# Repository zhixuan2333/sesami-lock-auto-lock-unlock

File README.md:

# Sesami Lock MitoLab

自動施錠・解錠スケジューラー — Seeed XIAO ESP32C6 + DS1302 RTC + SESAME スマートロック

[English](README.en.md)

---

> **免責事項**: このプロジェクトのコード・ドキュメントはすべて AI (Claude) によって生成されています。動作保証はなく、作者は一切の責任を負いません。自己責任でご使用ください。

---

## 概要

設定した時刻に SESAME スマートロックを自動で施錠・解錠します。DS1302 RTC で正確な時刻を保持し、ESP32C6 のディープスリープを活用して低消費電力を実現します。起動時にシリアルシェルが立ち上がり、時刻やスケジュールをその場で設定できます。

---

## ハードウェア

| 部品 | 型番 |
| --- | --- |
| マイコン | Seeed Studio XIAO ESP32C6 |
| RTC | DS1302 (+ 32.768 kHz 水晶) |
| スマートロック | SESAME 3/4/5/5 PRO など |

---

## 回路図

```text
                    XIAO ESP32C6
                  ┌─────────────┐
              D0  │●           ●│ 5V
              D1  │●           ●│ GND
              D2  │●           ●│ 3V3
              D3  │●           ●│ D10 ──── CLK (SCL)
              D4  │●           ●│ D9  ──── DAT (IO)
              D5  │●           ●│ D8  ──── RST
              D6  │●           ●│ D7
                  └─────────────┘
                                             DS1302
                                          ┌──────────┐
                              3V3 ────── │ VCC      │
                              GND ────── │ GND      │
                        CLK (D10) ────── │ CLK      │
                         DAT (D9) ────── │ DAT      │
                         RST (D8) ────── │ RST      │
                                         │ X1 ──┐   │
                                         │ X2 ──┤   │  32.768 kHz
                                         └──────┼───┘  水晶発振子
                                               ═╧═
```

### 配線まとめ

| XIAO ピン | DS1302 ピン | 説明 |
| --- | --- | --- |
| D8 | RST | チップセレクト |
| D9 | DAT (IO) | シリアルデータ |
| D10 | CLK (SCL) | クロック |
| 3V3 | VCC | 電源 3.3 V |
| GND | GND | グランド |

> SESAME ロックとの通信は Bluetooth LE (BLE) 経由のため、追加配線は不要です。

---

## 動作フロー

```text
起動
  │
  ├─[初回起動]──→ シリアルシェル (10 秒待機)
  │                  ↓ "run" または タイムアウト
  └─[スリープ復帰]
        │
        ↓
    RTC で現在時刻を確認
        │
        ├─[解錠時刻を過ぎていて未解錠]
        │     → BLE スキャン → 接続 → unlock()
        │
        ├─[施錠時刻を過ぎていて未施錠]
        │     → BLE スキャン → 接続 → lock()
        │
        └─[まだ時刻でない]
              → 次のイベントまでディープスリープ (最大 1 時間)
```

---

## 環境構築

### 必要なもの

- [VS Code](https://code.visualstudio.com/)
- [PlatformIO IDE 拡張機能](https://marketplace.visualstudio.com/items?itemName=platformio.platformio-ide)
- USB-C ケーブル (XIAO との接続用)

### セットアップ手順

1. VS Code に **PlatformIO IDE** 拡張機能をインストール
2. このリポジトリをクローン

   ```bash
   git clone https://github.com/zhixuan2333/sesami-lock-auto-lock-unlock.git
   cd sesami-lock-auto-lock-unlock
   ```

3. VS Code でフォルダを開く → PlatformIO が自動でライブラリを取得
4. Sesame キー情報を設定

   ```bash
   cp src/mysesame-config.h.example src/mysesame-config.h
   # SESAME_SECRET / SESAME_PK / SESAME_MODEL を編集
   ```

5. PlatformIO のサイドバーから **Upload** → ビルド & 書き込み
6. **Serial Monitor** でシリアル出力を確認 (115200 baud)

<details>
<summary>CLI (uv + pio) でセットアップする場合</summary>

```bash
# uv のインストール
# macOS / Linux
curl -LsSf https://astral.sh/uv/install.sh | sh
# Windows (PowerShell)
powershell -ExecutionPolicy ByPass -c "irm https://astral.sh/uv/install.ps1 | iex"

# 仮想環境 & PlatformIO
uv venv
uv pip install platformio

# よく使うコマンド
uv run pio run                   # ビルド
uv run pio run --target upload   # 書き込み
uv run pio device monitor        # シリアルモニタ
uv run pio pkg update            # ライブラリの更新
```

</details>

---

## SESAME キーの取得

1. SESAME アプリでデバイスの QR コードを表示する
2. [https://sesame-qr-reader.vercel.app/](https://sesame-qr-reader.vercel.app/) で QR を読み取る
3. 表示された `Secret Key` と `Public Key` を `mysesame-config.h` に設定

```cpp
// src/mysesame-config.h
#define SESAME_SECRET "your_secret_key_here"
#define SESAME_PK     "your_public_key_here"
#define SESAME_MODEL  Sesame::model_t::sesame_5_pro  // 使用機種に合わせて変更
```

---

## シリアルシェルのコマンド

起動後 10 秒間、シリアルモニタでコマンドを入力できます (115200 baud)。

```text
> help
Commands:
  time                         - show current RTC time
  time set YYYY-MM-DD HH:MM:SS - set RTC time
  schedule                     - show unlock/lock schedule
  unlock HH:MM                 - set daily unlock time (default 08:00)
  lock HH:MM                   - set daily lock time   (default 20:00)
  reset                        - reset today's action flags
  run                          - exit shell and start operation
```

### 例

```text
> time set 2026-05-08 09:00:00
> unlock 07:30
> lock 22:00
> run
```

---

## set_rtc_time.py — RTC 時刻自動設定スクリプト

PC の現在時刻を RTC に書き込む Python スクリプトです。
[uv](https://github.com/astral-sh/uv) を使えば `pyserial` を事前インストールせず、そのまま実行できます。

### インストール不要で即実行

```bash
# Windows (PowerShell)
powershell -ExecutionPolicy ByPass -c "irm https://astral.sh/uv/install.ps1 | iex"

# macOS / Linux
curl -LsSf https://astral.sh/uv/install.sh | sh
```

### 使い方

```bash
# 時刻だけ合わせる
uv run set_rtc_time.py COM3          # Windows
uv run set_rtc_time.py /dev/ttyUSB0  # Linux / macOS

# 時刻 + unlock/lock スケジュールも設定
uv run set_rtc_time.py COM3 --unlock 08:00 --lock 22:00
```

### オプション

| オプション | 説明 | デフォルト |
| --- | --- | --- |
| `port` | シリアルポート (必須) | — |
| `--baud` | ボーレート | `115200` |
| `--unlock HH:MM` | 毎日の解錠時刻 | 変更しない |
| `--lock HH:MM` | 毎日の施錠時刻 | 変更しない |

> スクリプトは起動後 8 秒以内にシリアルシェルを検出し、`time set`・`unlock`・`lock`・`run` コマンドを自動送信します。

---

## 対応 SESAME モデル

`SESAME_MODEL` に指定できる値:

| 値 | 機種 |
| --- | --- |
| `sesame_3` | SESAME 3 |
| `sesame_4` | SESAME 4 |
| `sesame_5` | SESAME 5 |
| `sesame_5_pro` | SESAME 5 PRO |
| `sesame_6` | SESAME 6 |
| `sesame_6_pro` | SESAME 6 PRO |
| `sesame_bot` | SESAME bot |
| `sesame_bot_2` | SESAME Bot 2 |

---

## 依存ライブラリ

| ライブラリ | バージョン | 用途 |
| --- | --- | --- |
| [libsesame3bt](https://github.com/homy-newfs8/libsesame3bt) | 0.32.0 | SESAME BLE 通信 |
| [makuna/RTC](https://github.com/Makuna/Rtc) | ^2.4.2 | DS1302 RTC 制御 |

---

## ライセンス

MIT

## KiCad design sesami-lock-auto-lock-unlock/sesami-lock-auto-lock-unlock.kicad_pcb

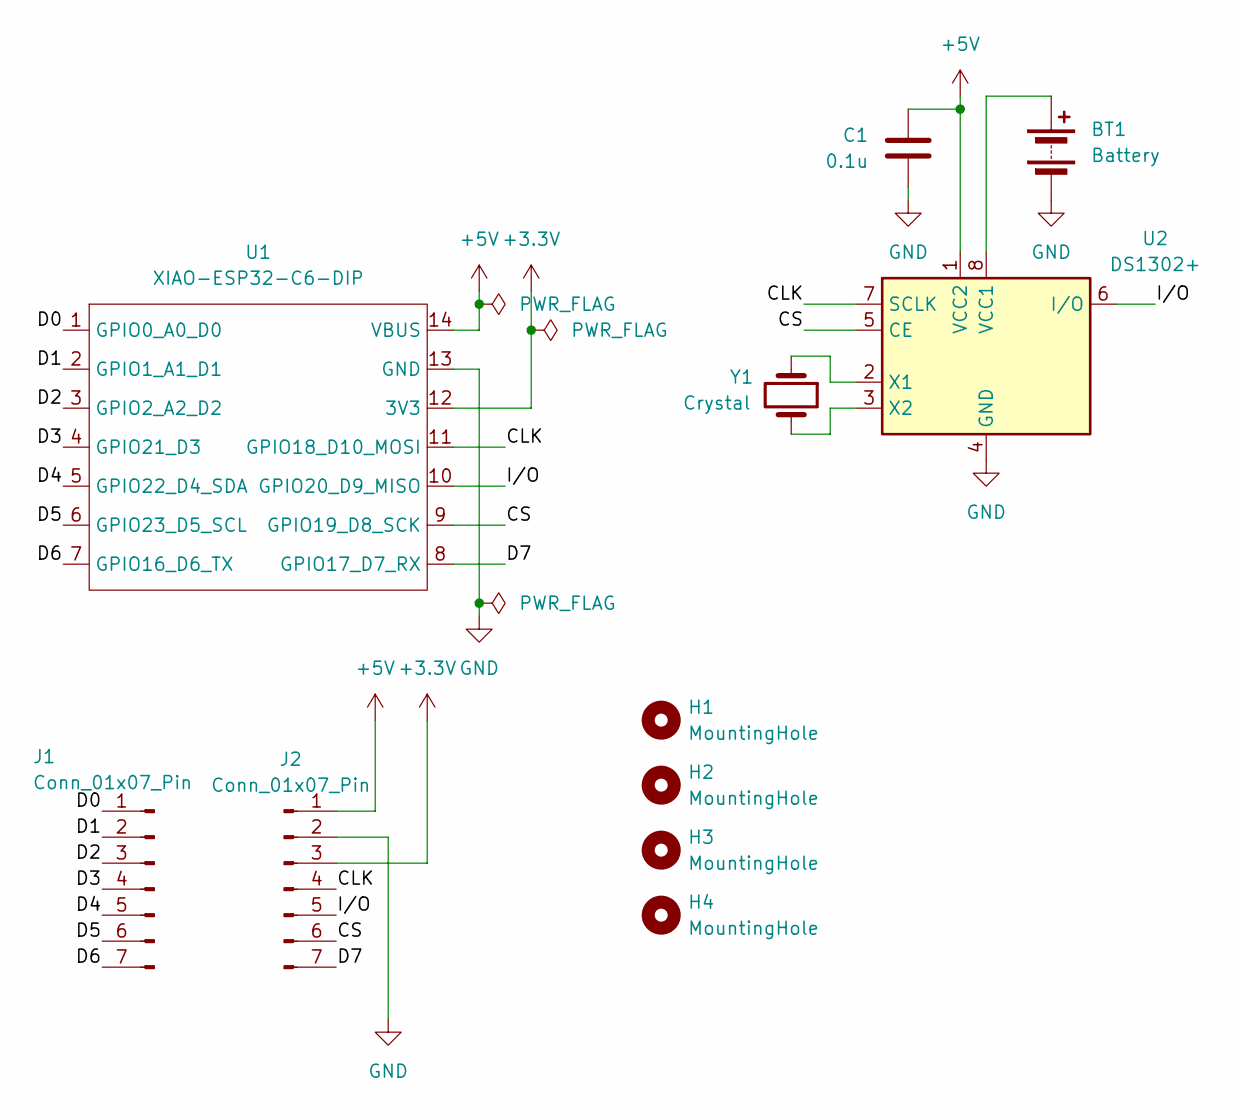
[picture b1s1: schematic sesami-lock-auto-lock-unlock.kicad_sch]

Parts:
BT1: Battery; BatteryHolder_MYOUNG_BS-07-A1BJ001_CR2032
C1: 0.1u; C_Disc_D7.5mm_W2.5mm_P5.00mm
H1, H2, H3, H4: MountingHole; MountingHole_3.2mm_M3
J1, J2: Conn_01x07_Pin; PinHeader_1x07_P2.54mm_Vertical
U1: XIAO-ESP32-C6-DIP
U2: DS1302+; DIP-8_W7.62mm
Y1: Crystal; Crystal_C38-LF_D3.0mm_L8.0mm_Horizontal

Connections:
+3.3V: J2.3, U1.12 (3V3)
+5V: C1.1, J2.1, U1.14 (VBUS), U2.1 (VCC2)
/CLK: J2.4, U1.11 (GPIO18_D10_MOSI), U2.7 (SCLK)
/CS: J2.6, U1.9 (GPIO19_D8_SCK), U2.5 (CE)
/D0: J1.1, U1.1 (GPIO0_A0_D0)
/D1: J1.2, U1.2 (GPIO1_A1_D1)
/D2: J1.3, U1.3 (GPIO2_A2_D2)
/D3: J1.4, U1.4 (GPIO21_D3)
/D4: J1.5, U1.5 (GPIO22_D4_SDA)
/D5: J1.6, U1.6 (GPIO23_D5_SCL)
/D6: J1.7, U1.7 (GPIO16_D6_TX)
/D7: J2.7, U1.8 (GPIO17_D7_RX)
/I/O: J2.5, U1.10 (GPIO20_D9_MISO), U2.6 (I/O)
GND: BT1.2 (-), C1.2, J2.2, U1.13 (GND), U2.4 (GND)
unnamed: BT1.1 (+), U2.8 (VCC1)
unnamed: U2.2 (X1), Y1.1
unnamed: U2.3 (X2), Y1.2

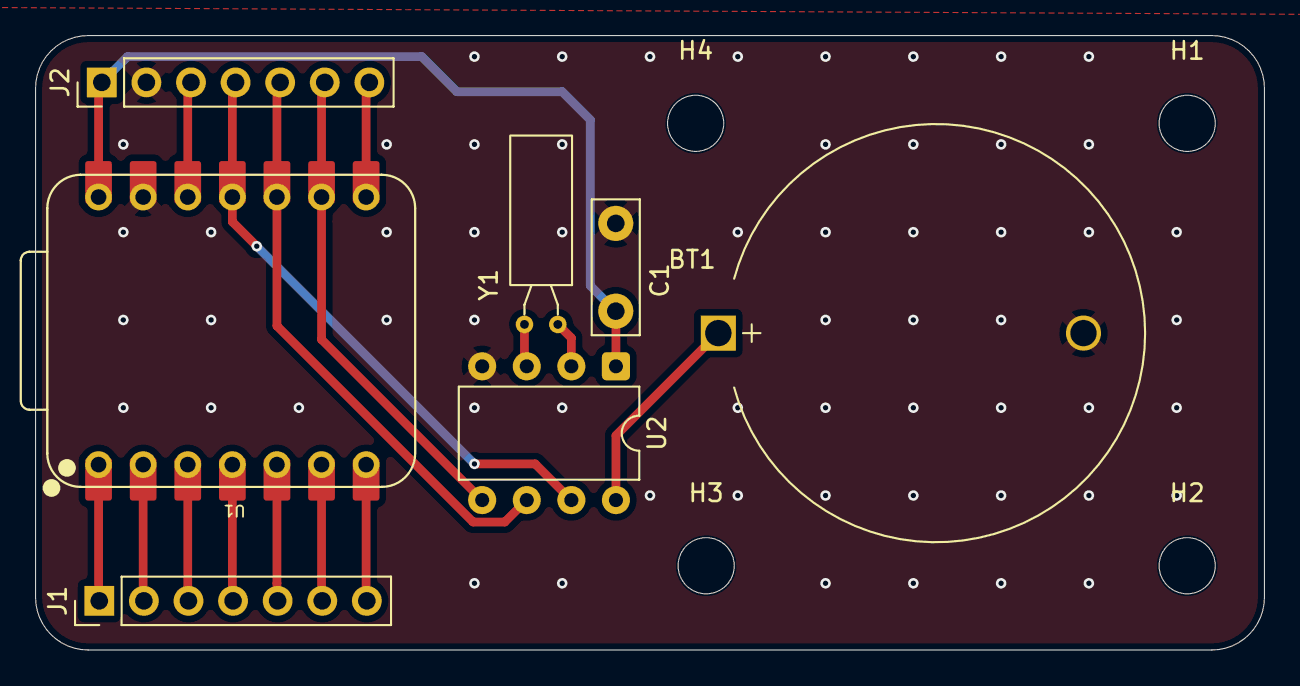
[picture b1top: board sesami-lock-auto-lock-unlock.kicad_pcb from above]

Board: 2 copper layers, 70.0 x 35.0 mm, 11 parts (0 on the bottom side), 17 nets.

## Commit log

2026-05-08 add python script
2026-05-12 add kicad
